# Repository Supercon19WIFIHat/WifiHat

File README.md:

# WifiHat
A hat that connects to the PMOD connector containing a ESP32
* 1-bit SDIO connected to PMOD
* UART and programming pins connected to PMOD
* Will be flashed with esp-at firmware.

# SOC Image
* I have modified the SOC image adding a 3rd UART for the module.
* The pmod pins no. 4 and 5 (B1 B2) are now TX and RX.
* The new UART is at address `0x10000020`

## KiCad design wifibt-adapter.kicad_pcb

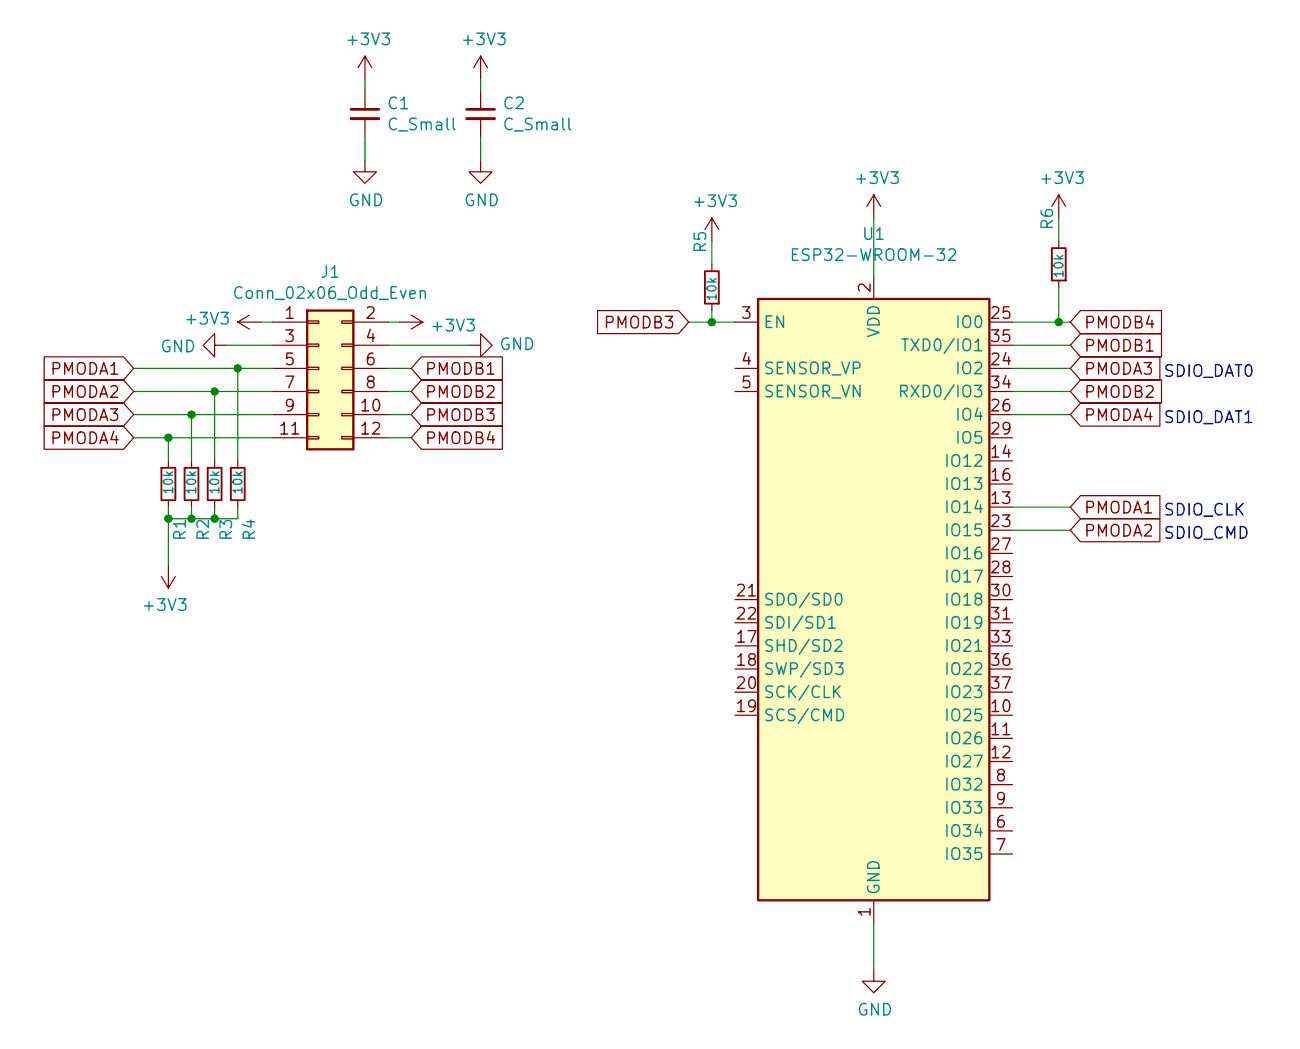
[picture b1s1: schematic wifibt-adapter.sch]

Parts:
C1, C2: C_Small; C_0603_1608Metric
J1: Conn_02x06_Odd_Even; PinHeader_2x06_P2.54mm_Horizontal
R1, R2, R3, R4, R5, R6: 10k; C_0603_1608Metric
U1: ESP32-WROOM-32

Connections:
+3V3: C1.1, C2.1, J1.1, J1.2, R1.2, R2.2, R3.2, R4.2, R5.2, R6.2, U1.2 (VDD)
GND: C1.2, C2.2, J1.3, J1.4, U1.1 (GND), U1.15 (GND), U1.38 (GND)
PMODA1: J1.5, R4.1, U1.13 (IO14)
PMODA2: J1.7, R3.1, U1.23 (IO15)
PMODA3: J1.9, R2.1, U1.24 (IO2)
PMODA4: J1.11, R1.1, U1.26 (IO4)
PMODB1: J1.6, U1.35 (TXD0/IO1)
PMODB2: J1.8, U1.34 (RXD0/IO3)
PMODB3: J1.10, R5.1, U1.3 (EN)
PMODB4: J1.12, R6.1, U1.25 (IO0)

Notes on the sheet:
SDIO_CLK
SDIO_CMD
SDIO_DAT0
SDIO_DAT1

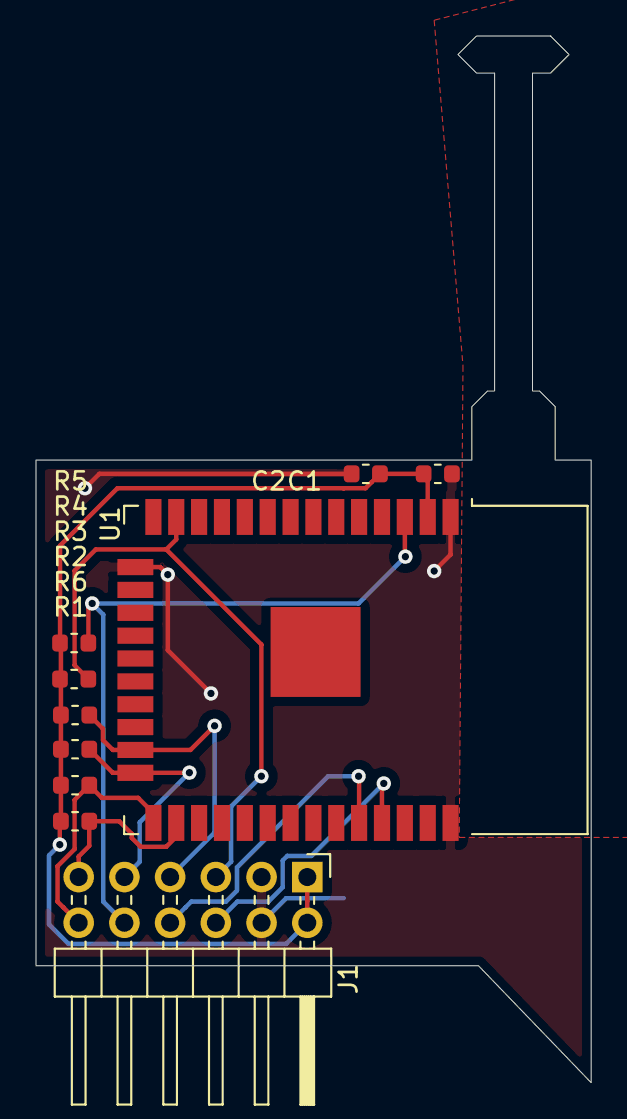
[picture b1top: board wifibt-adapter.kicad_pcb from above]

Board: 2 copper layers, 30.8 x 58.1 mm, 11 parts (0 on the bottom side), 10 nets.

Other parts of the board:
svg2mod: G***; wifibt-fp

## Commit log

2019-11-07 init commit
2019-11-07 rev1 done
2019-11-07 added module image
2019-11-07 added schematic img
2019-11-07 updated schematic img
